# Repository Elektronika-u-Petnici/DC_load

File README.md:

# DC load

Petničko linearno opterećenje

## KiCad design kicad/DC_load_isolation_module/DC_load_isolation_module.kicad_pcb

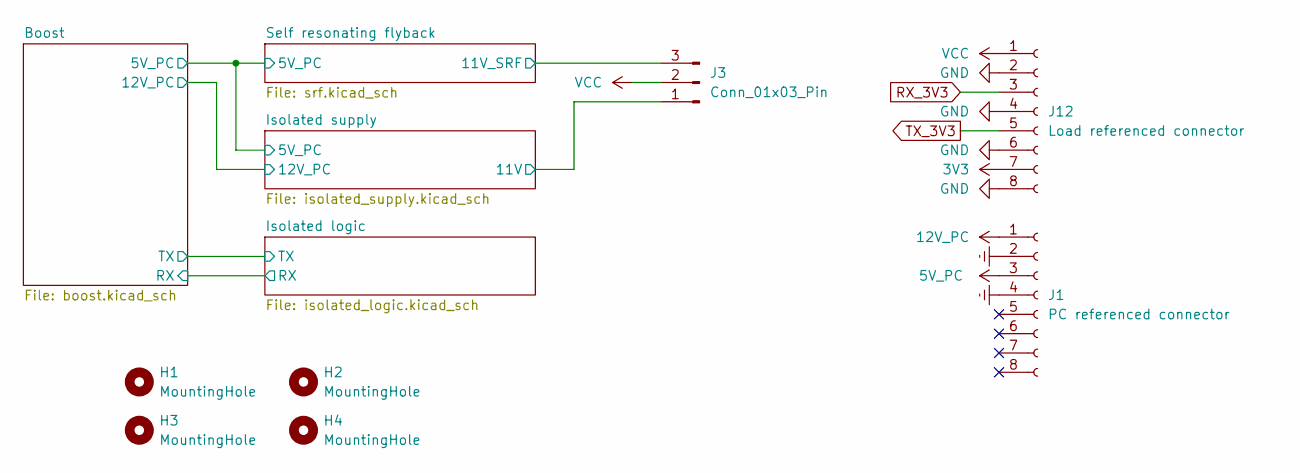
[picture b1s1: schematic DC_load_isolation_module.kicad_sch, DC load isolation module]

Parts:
H1, H2, H3, H4: MountingHole; M3_hole_with_spacer
J1: PC referenced connector; PinSocket_1x08_P2.54mm_Vertical
J3: Conn_01x03_Pin; PinHeader_1x03_P2.54mm_Vertical
J12: Load referenced connector; PinSocket_1x08_P2.54mm_Vertical

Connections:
3V3: J12.7; also elsewhere on the board
5V_PC: J1.3; also elsewhere on the board
12V_PC: J1.1; also elsewhere on the board
/Isolated supply/11V: J3.1; also elsewhere on the board
/Self resonating flyback/11V_SRF: J3.3; also elsewhere on the board
Earth: J1.2, J1.4; also elsewhere on the board
GND: J12.2, J12.4, J12.6, J12.8; also elsewhere on the board
RX_3V3: J12.3; also elsewhere on the board
TX_3V3: J12.5; also elsewhere on the board
VCC: J3.2, J12.1

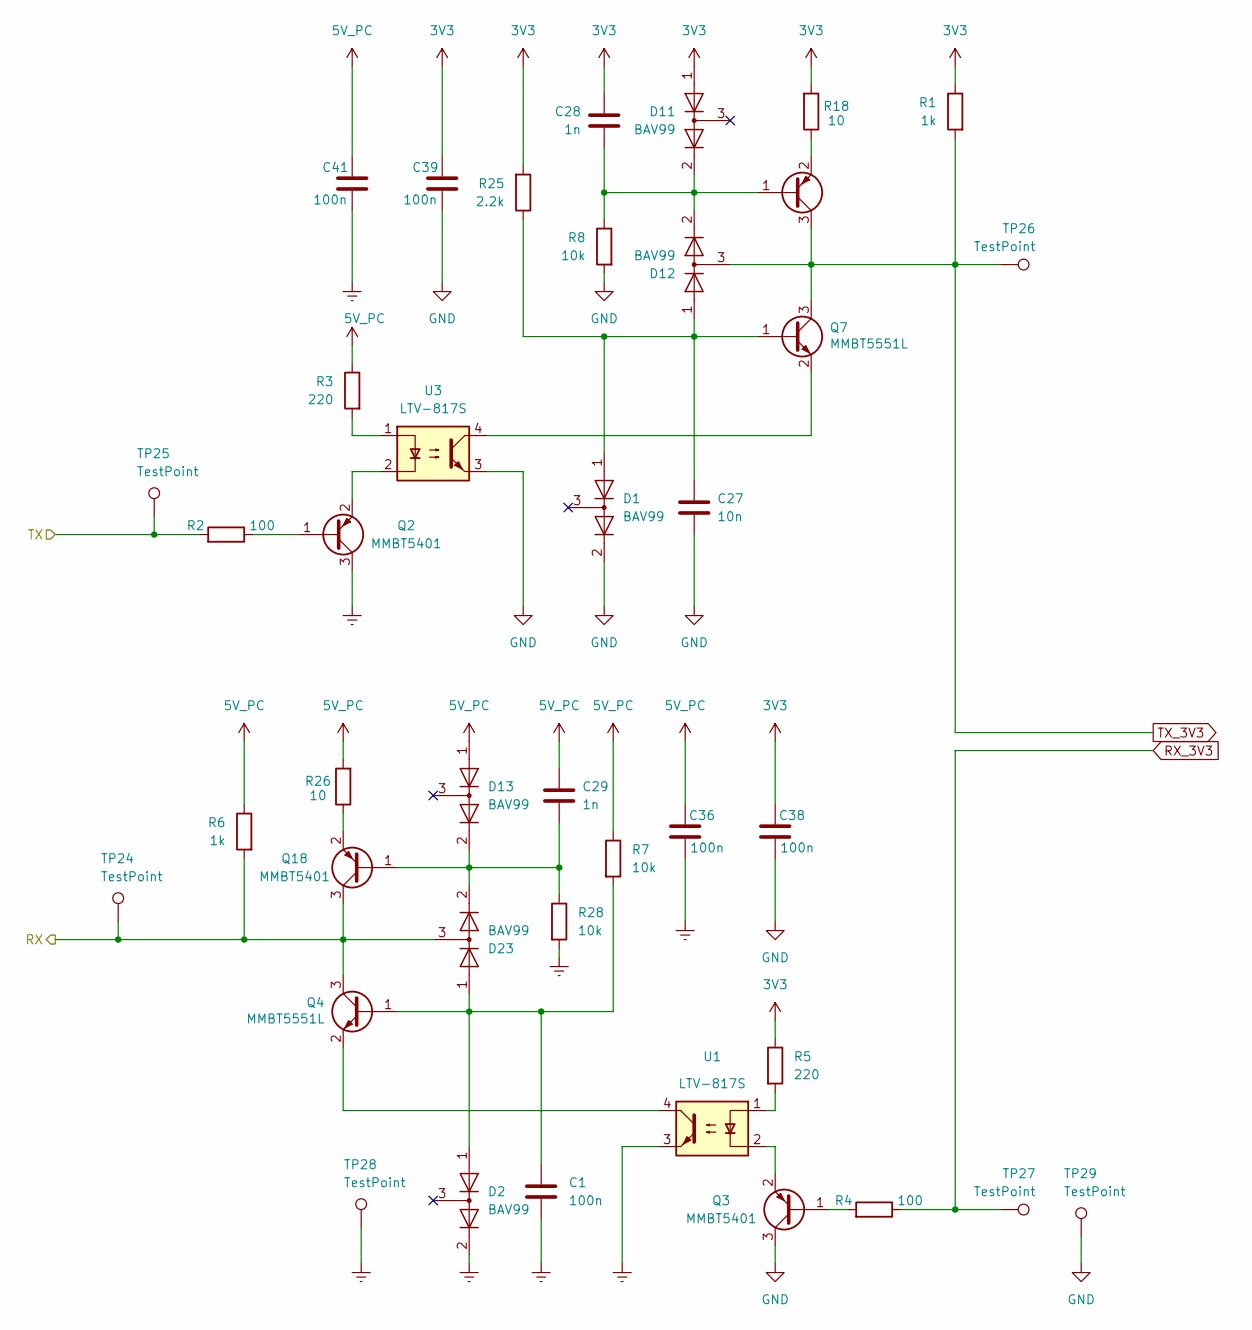
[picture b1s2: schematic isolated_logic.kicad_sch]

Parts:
C1, C36, C38, C39, C41: 100n; C_0603_1608Metric_Pad1.08x0.95mm_HandSolder; LCSC C14663
C27: 10n; C_0603_1608Metric_Pad1.08x0.95mm_HandSolder; LCSC C57112
C28, C29: 1n; C_0603_1608Metric_Pad1.08x0.95mm_HandSolder; LCSC C1588
D1, D2, D11, D12, D13, D23: BAV99; SOT-23; LCSC C2500
Q2, Q3, Q17, Q18: MMBT5401; SOT-23; LCSC C8326
Q4, Q7: MMBT5551L; SOT-23; LCSC C2145
R1, R6: 1k; R_0603_1608Metric_Pad0.98x0.95mm_HandSolder; LCSC C22962
R2, R4: 100; R_0603_1608Metric_Pad0.98x0.95mm_HandSolder; LCSC C22775
R3, R5: 220; R_0603_1608Metric_Pad0.98x0.95mm_HandSolder; LCSC C22962
R7, R8, R28: 10k; R_0603_1608Metric_Pad0.98x0.95mm_HandSolder; LCSC C25804
R18, R26: 10; R_0603_1608Metric_Pad0.98x0.95mm_HandSolder; LCSC C22859
R25: 2.2k; R_0603_1608Metric_Pad0.98x0.95mm_HandSolder; LCSC C4190
TP24, TP25, TP26, TP27, TP28, TP29: TestPoint; TestPoint_Pad_D2.0mm
U1, U3: LTV-817S; SMDIP-4_W9.53mm

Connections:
3V3: C28.2, C38.1, C39.1, D11.1 (K), R1.1, R5.1, R18.2, R25.2; also elsewhere on the board
5V_PC: C29.2, C36.1, C41.1, D13.1 (K), R3.1, R6.1, R7.1, R26.2; also elsewhere on the board
/Boost/RX: D23.3 (K), Q4.3 (C), Q18.3 (C), R6.2, TP24.1; also elsewhere on the board
/Boost/TX: R2.2, TP25.1; also elsewhere on the board
Earth: C1.1, C36.2, C41.2, D2.2 (A), Q2.3 (C), R28.2, TP28.1, U1.3; also elsewhere on the board
GND: C27.1, C38.2, C39.2, D1.2 (A), Q3.3 (C), R8.2, TP29.1, U3.3; also elsewhere on the board
unnamed: C28.1, D11.2 (A), D12.2 (A), Q17.1 (B), R8.1
unnamed: C29.1, D13.2 (A), D23.2 (A), Q18.1 (B), R28.1
unnamed: Q2.1 (B), R2.1
unnamed: Q2.2 (E), U3.2
unnamed: Q3.1 (B), R4.2
unnamed: Q3.2 (E), U1.2
unnamed: C1.2, D2.1 (K), D23.1 (K), Q4.1 (B), R7.2
unnamed: Q4.2 (E), U1.4
unnamed: C27.2, D1.1 (K), D12.1 (K), Q7.1 (B), R25.1
unnamed: Q7.2 (E), U3.4
unnamed: Q17.2 (E), R18.1
unnamed: Q18.2 (E), R26.1
unnamed: R3.2, U3.1
unnamed: R5.2, U1.1
RX_3V3: R4.1, TP27.1; also elsewhere on the board
TX_3V3: D12.3 (K), Q7.3 (C), Q17.3 (C), R1.2, TP26.1; also elsewhere on the board

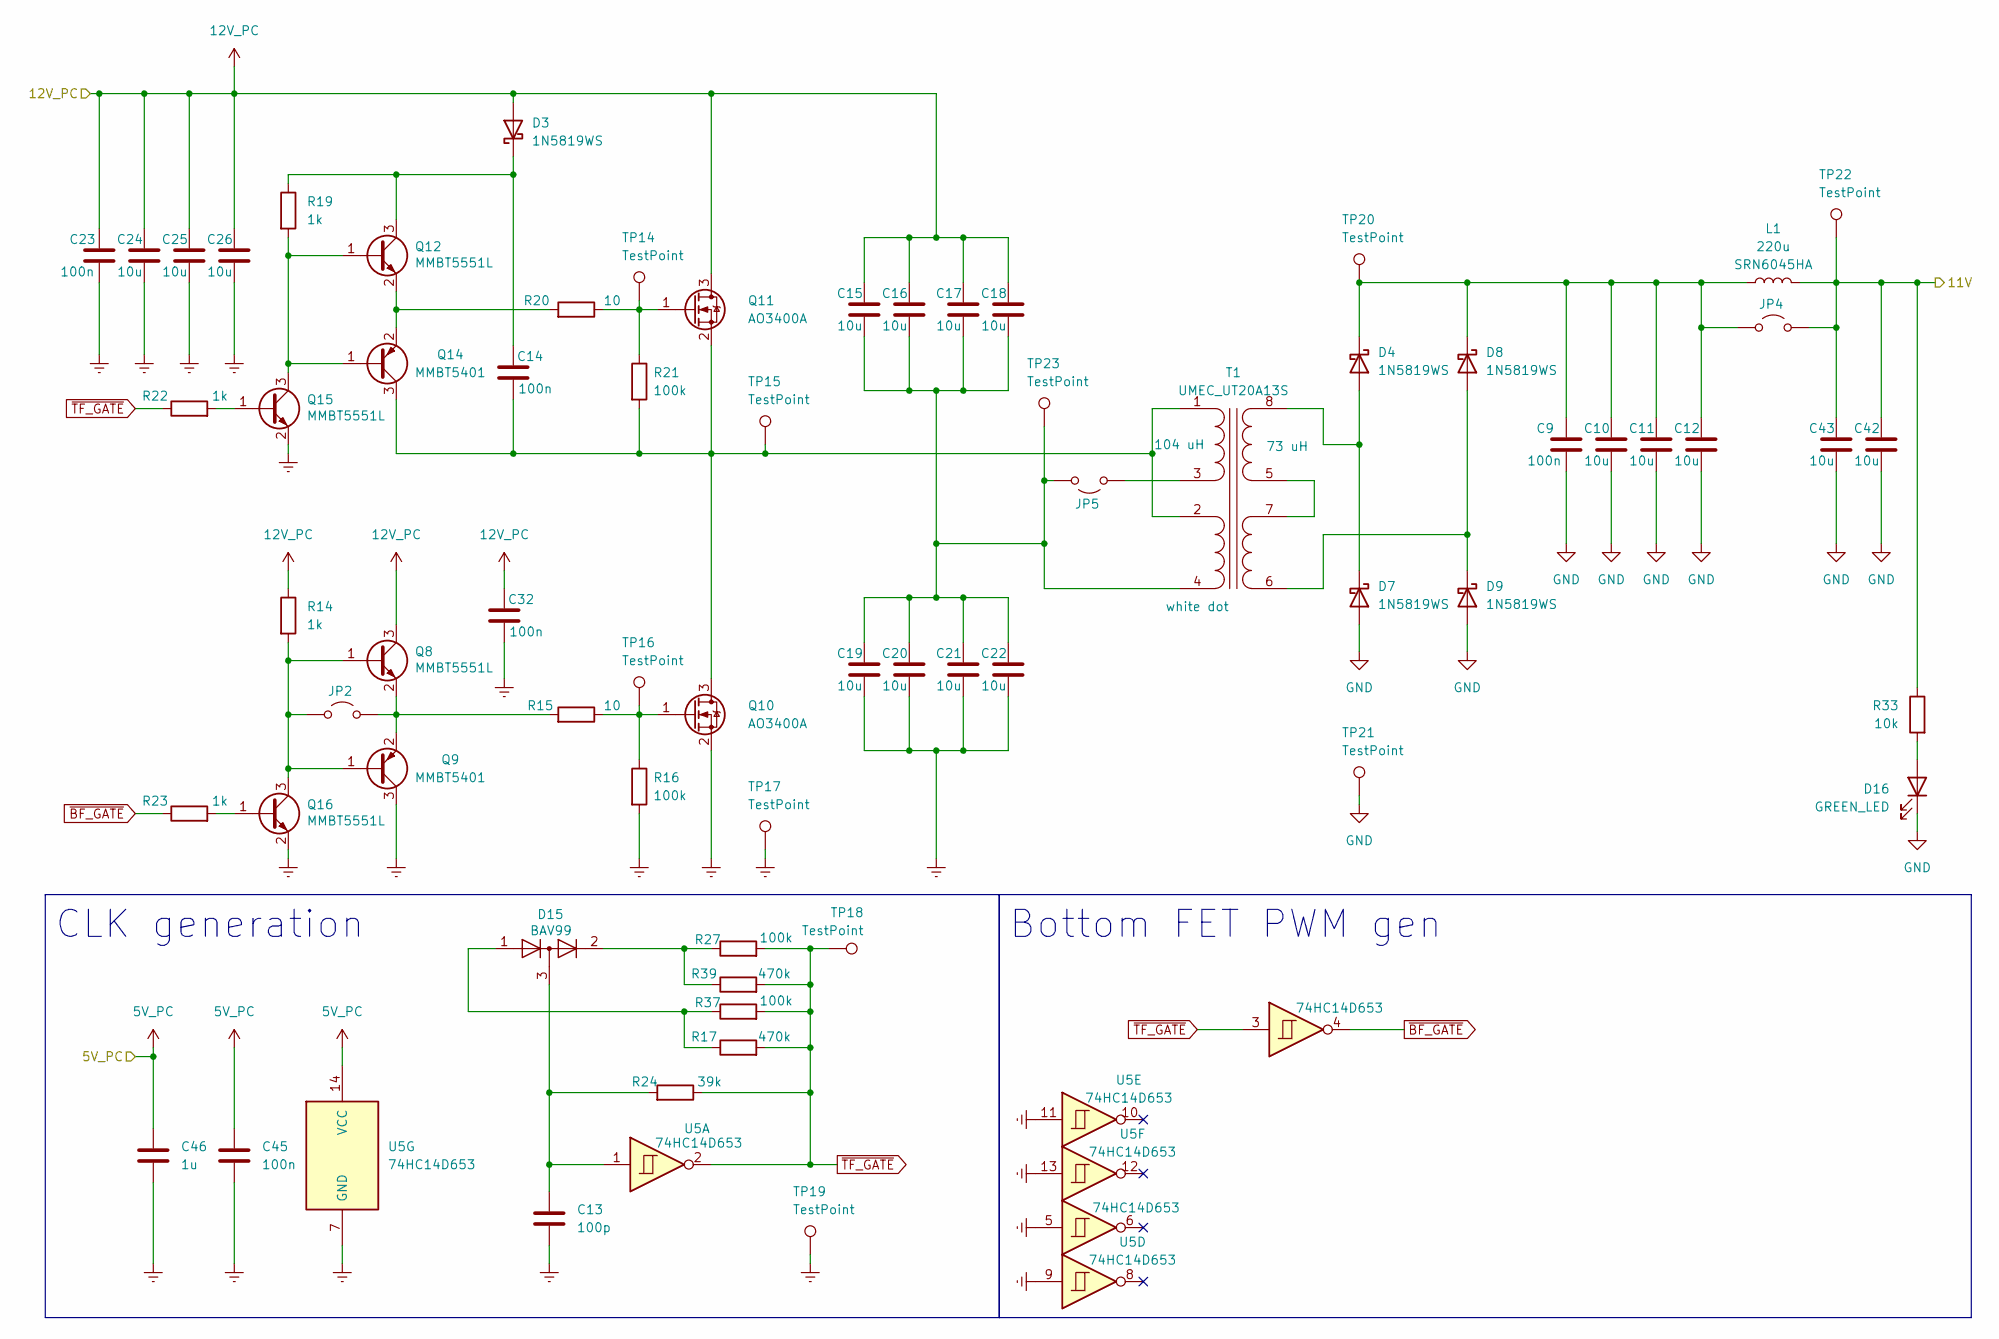
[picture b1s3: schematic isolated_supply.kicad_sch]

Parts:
C9, C14, C23, C32, C45: 100n; C_0603_1608Metric_Pad1.08x0.95mm_HandSolder; LCSC C14663
C10, C11, C12, C15, C16, C17, C18, C19, C20, C21, C22, C24, C25, C26, C42, C43: 10u; C_0603_1608Metric_Pad1.08x0.95mm_HandSolder; LCSC C96446
C13: 100p; C_0603_1608Metric_Pad1.08x0.95mm_HandSolder; LCSC C14858
C46: 1u; C_0603_1608Metric_Pad1.08x0.95mm_HandSolder; LCSC C15849
D3, D4, D7, D8, D9: 1N5819WS; D_SOD-323; LCSC C191023
D15: BAV99; SOT-23; LCSC C2500
D16: GREEN_LED; LED_0805_2012Metric_Pad1.15x1.40mm_HandSolder; LCSC C2297
JP2, JP4, JP5: Jumper_2_Open; SolderJumper-2_P1.3mm_Open_RoundedPad1.0x1.5mm
L1: 220u; L_Bourns_SRN6045TA; Partname SRN6045HA
Q8, Q12, Q15, Q16: MMBT5551L; SOT-23; LCSC C2145
Q9, Q14: MMBT5401; SOT-23; LCSC C8326
Q10, Q11: AO3400A; SOT-23; LCSC C20917
R14, R19, R22, R23: 1k; R_0603_1608Metric_Pad0.98x0.95mm_HandSolder; LCSC C22962
R15, R20: 10; R_0603_1608Metric_Pad0.98x0.95mm_HandSolder; LCSC C22859
R16, R21, R27, R37: 100k; R_0603_1608Metric_Pad0.98x0.95mm_HandSolder; LCSC C25803
R17, R39: 470k; R_0603_1608Metric_Pad0.98x0.95mm_HandSolder; LCSC C23178
R24: 39k; R_0603_1608Metric_Pad0.98x0.95mm_HandSolder; LCSC C23153
R33: 10k; R_0603_1608Metric_Pad0.98x0.95mm_HandSolder; LCSC C25804
T1: UMEC_UT20A13S
TP14, TP15, TP16, TP17, TP18, TP19, TP20, TP21, TP22, TP23: TestPoint; TestPoint_Pad_D2.0mm
U5: 74HC14D653; SOIC-14_3.9x8.7mm_P1.27mm; LCSC C5605

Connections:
5V_PC: C45.2, C46.2, U5.14 (VCC); also elsewhere on the board
12V_PC: C15.1, C16.1, C17.1, C18.1, C23.1, C24.1, C25.1, C26.1, C32.1, D3.2 (A), Q8.3 (C), Q11.3 (D), R14.1; also elsewhere on the board
/Isolated supply/11V: C42.1, C43.1, JP4.2 (B), L1.2, R33.1, TP22.1; also elsewhere on the board
Earth: C13.1, C19.2, C20.2, C21.2, C22.2, C23.2, C24.2, C25.2, C26.2, C32.2, C45.1, C46.1, Q9.3 (C), Q10.2 (S), Q15.2 (E), Q16.2 (E), R16.2, TP17.1, TP19.1, U5.5, U5.7 (GND), U5.9, U5.11, U5.13; also elsewhere on the board
GND: C9.2, C10.2, C11.2, C12.2, C42.2, C43.2, D7.2 (A), D9.2 (A), D16.1 (K), TP21.1; also elsewhere on the board
unnamed: C13.2, D15.3 (K), R24.2, U5.1
unnamed: C14.1, D3.1 (K), Q12.3 (C), R19.1
unnamed: D4.2 (A), D7.1 (K), T1.8 (SB)
unnamed: C9.1, C10.1, C11.1, C12.1, D4.1 (K), D8.1 (K), JP4.1 (A), L1.1, TP20.1
unnamed: D8.2 (A), D9.1 (K), T1.6 (SA)
unnamed: D15.2 (A), R27.1, R39.1
unnamed: D15.1 (K), R17.1, R37.1
unnamed: D16.2 (A), R33.2
unnamed: JP2.1 (A), Q8.1 (B), Q9.1 (B), Q16.3 (C), R14.2
unnamed: JP2.2 (B), Q8.2 (E), Q9.2 (E), R15.2
unnamed: C15.2, C16.2, C17.2, C18.2, C19.1, C20.1, C21.1, C22.1, JP5.1 (A), T1.4 (AB), TP23.1
unnamed: JP5.2 (B), T1.3 (AB)
unnamed: C14.2, Q10.3 (D), Q11.2 (S), Q14.3 (C), R21.2, T1.1 (AA), T1.2 (AA), TP15.1
unnamed: Q10.1 (G), R15.1, R16.1, TP16.1
unnamed: Q11.1 (G), R20.1, R21.1, TP14.1
unnamed: Q12.1 (B), Q14.1 (B), Q15.3 (C), R19.2
unnamed: Q12.2 (E), Q14.2 (E), R20.2
unnamed: Q15.1 (B), R22.2
unnamed: Q16.1 (B), R23.2
unnamed: T1.5 (SA), T1.7 (SB)
~BF_GATE: R23.1, U5.4
~TF_GATE: R17.2, R22.1, R24.1, R27.2, R37.2, R39.2, TP18.1, U5.2, U5.3

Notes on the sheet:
Bottom FET PWM gen
CLK generation

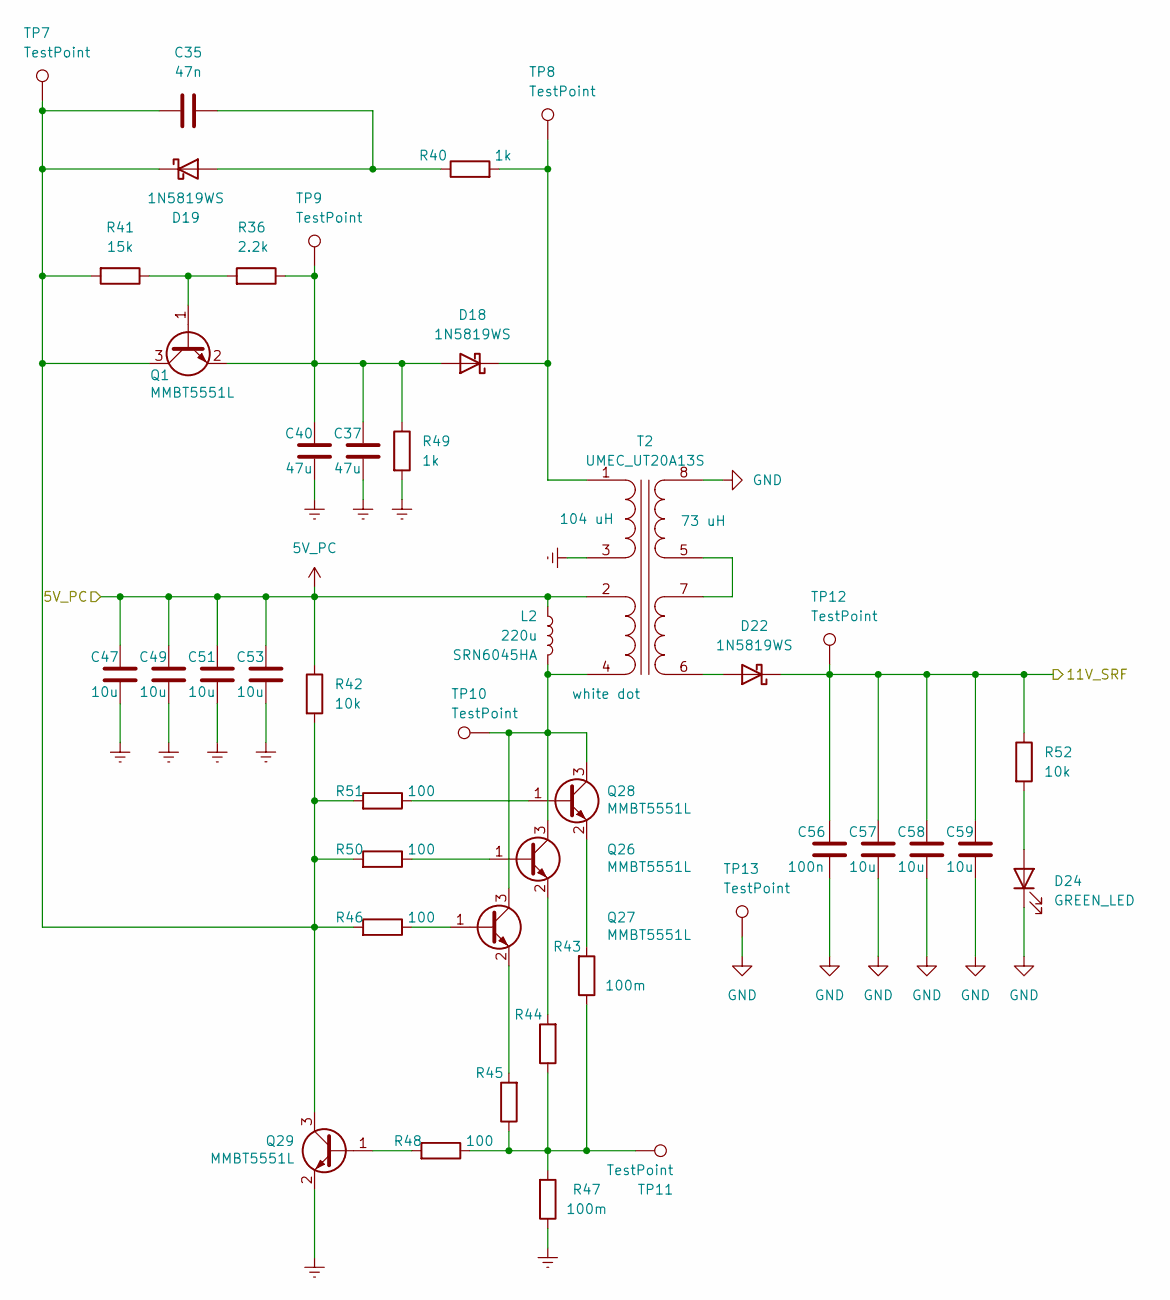
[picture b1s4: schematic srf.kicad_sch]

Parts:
C35: 47n; C_0603_1608Metric_Pad1.08x0.95mm_HandSolder; LCSC C1622
C37, C40: 47u; C_1206_3216Metric_Pad1.33x1.80mm_HandSolder; LCSC C96123
C47, C49, C51, C53, C57, C58, C59: 10u; C_0603_1608Metric_Pad1.08x0.95mm_HandSolder; LCSC C96446
C56: 100n; C_0603_1608Metric_Pad1.08x0.95mm_HandSolder; LCSC C14663
D18, D19, D22: 1N5819WS; D_SOD-323; LCSC C191023
D24: GREEN_LED; LED_0805_2012Metric_Pad1.15x1.40mm_HandSolder; LCSC C2297
L2: 220u; L_Bourns_SRN6045TA; Partname SRN6045HA
Q1, Q26, Q27, Q28, Q29: MMBT5551L; SOT-23; LCSC C2145
R36: 2.2k; R_0603_1608Metric_Pad0.98x0.95mm_HandSolder; LCSC C4190
R40, R49: 1k; R_0603_1608Metric_Pad0.98x0.95mm_HandSolder; LCSC C22962
R41: 15k; R_0603_1608Metric_Pad0.98x0.95mm_HandSolder; LCSC C22809
R42, R52: 10k; R_0603_1608Metric_Pad0.98x0.95mm_HandSolder; LCSC C25804
R43, R44, R45, R47: 100m; R_1206_3216Metric_Pad1.30x1.75mm_HandSolder; LCSC C25334
R46, R48, R50, R51: 100; R_0603_1608Metric_Pad0.98x0.95mm_HandSolder; LCSC C22775
T2: UMEC_UT20A13S
TP7, TP8, TP9, TP10, TP11, TP12, TP13: TestPoint; TestPoint_Pad_D2.0mm

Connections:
5V_PC: C47.1, C49.1, C51.1, C53.1, L2.2, R42.1, T2.2 (AA); also elsewhere on the board
/Self resonating flyback/11V_SRF: C56.1, C57.1, C58.1, C59.1, D22.1 (K), R52.1, TP12.1; also elsewhere on the board
Earth: C37.2, C40.2, C47.2, C49.2, C51.2, C53.2, Q29.2 (E), R47.1, R49.2, T2.3 (AB); also elsewhere on the board
GND: C56.2, C57.2, C58.2, C59.2, D24.1 (K), T2.8 (SB), TP13.1; also elsewhere on the board
unnamed: C37.1, C40.1, D18.2 (A), Q1.2 (E), R36.1, R49.1, TP9.1
unnamed: D18.1 (K), R40.2, T2.1 (AA), TP8.1
unnamed: C35.2, D19.2 (A), R40.1
unnamed: C35.1, D19.1 (K), Q1.3 (C), Q29.3 (C), R41.2, R42.2, R46.2, R50.2, R51.2, TP7.1
unnamed: D22.2 (A), T2.6 (SA)
unnamed: D24.2 (A), R52.2
unnamed: Q1.1 (B), R36.2, R41.1
unnamed: Q26.1 (B), R50.1
unnamed: L2.1, Q26.3 (C), Q27.3 (C), Q28.3 (C), T2.4 (AB), TP10.1
unnamed: Q26.2 (E), R44.2
unnamed: Q27.1 (B), R46.1
unnamed: Q27.2 (E), R45.2
unnamed: Q28.1 (B), R51.1
unnamed: Q28.2 (E), R43.2
unnamed: Q29.1 (B), R48.2
unnamed: R43.1, R44.1, R45.1, R47.2, R48.1, TP11.1
unnamed: T2.5 (SA), T2.7 (SB)

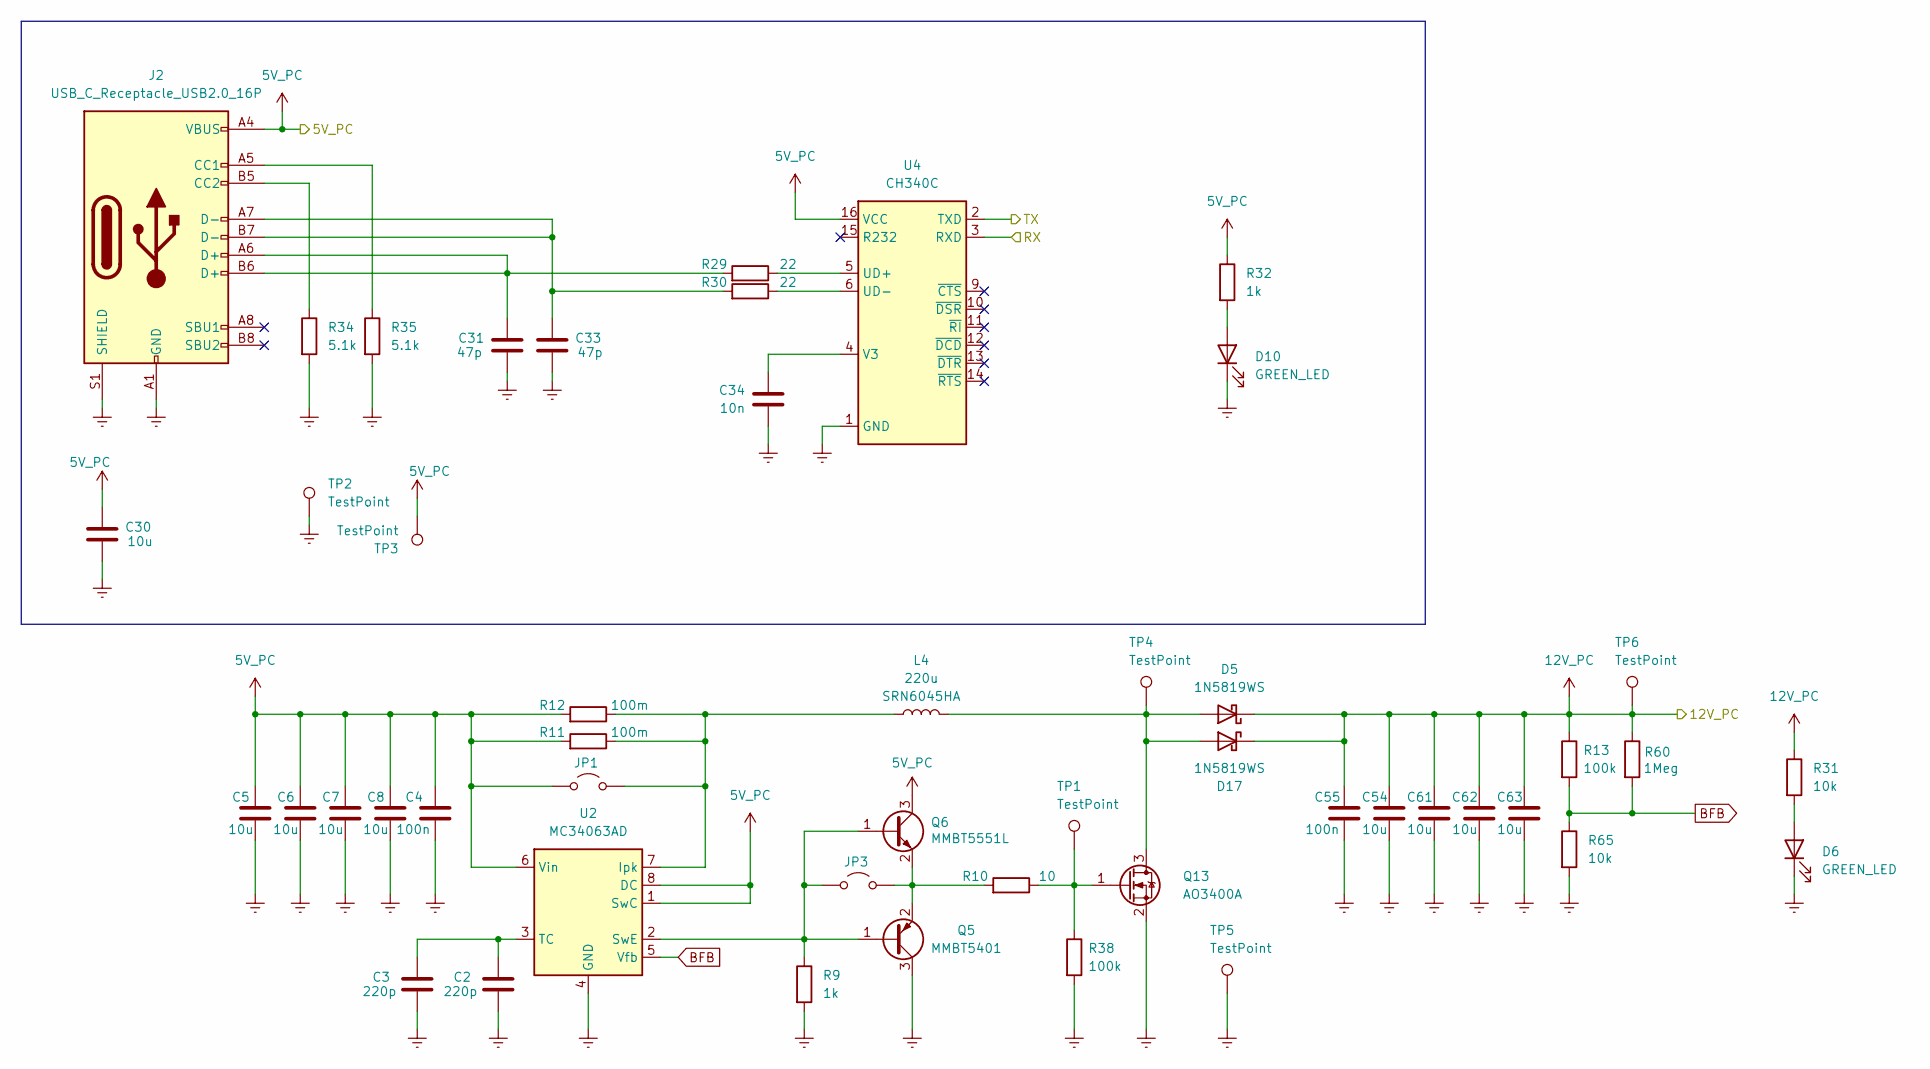
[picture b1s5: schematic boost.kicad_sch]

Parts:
C2, C3: 220p; C_0603_1608Metric_Pad1.08x0.95mm_HandSolder; LCSC C1603
C4, C55: 100n; C_0603_1608Metric_Pad1.08x0.95mm_HandSolder; LCSC C14663
C5, C6, C7, C8, C30, C54, C61, C62, C63: 10u; C_0603_1608Metric_Pad1.08x0.95mm_HandSolder; LCSC C96446
C31, C33: 47p; C_0603_1608Metric_Pad1.08x0.95mm_HandSolder; LCSC C1671
C34: 10n; C_0603_1608Metric_Pad1.08x0.95mm_HandSolder; LCSC C57112
D5, D17: 1N5819WS; D_SOD-323; LCSC C191023
D6, D10: GREEN_LED; LED_0805_2012Metric_Pad1.15x1.40mm_HandSolder; LCSC C2297
J2: USB_C_Receptacle_USB2.0_16P; USB_C_Receptacle_G-Switch_GT-USB-7010ASV
JP1, JP3: Jumper_2_Open; SolderJumper-2_P1.3mm_Open_RoundedPad1.0x1.5mm
L4: 220u; L_Bourns_SRN6045TA; Partname SRN6045HA
Q5: MMBT5401; SOT-23; LCSC C8326
Q6: MMBT5551L; SOT-23; LCSC C2145
Q13: AO3400A; SOT-23; LCSC C20917
R9, R32: 1k; R_0603_1608Metric_Pad0.98x0.95mm_HandSolder; LCSC C22962
R10: 10; R_0603_1608Metric_Pad0.98x0.95mm_HandSolder; LCSC C22859
R11, R12: 100m; R_1206_3216Metric_Pad1.30x1.75mm_HandSolder; LCSC C25334
R13, R38: 100k; R_0603_1608Metric_Pad0.98x0.95mm_HandSolder; LCSC C25803
R29, R30: 22; R_0603_1608Metric_Pad0.98x0.95mm_HandSolder; LCSC C23345
R31, R65: 10k; R_0603_1608Metric_Pad0.98x0.95mm_HandSolder; LCSC C25804
R34, R35: 5.1k; R_0603_1608Metric_Pad0.98x0.95mm_HandSolder; LCSC C23186
R60: 1Meg; R_0603_1608Metric_Pad0.98x0.95mm_HandSolder; LCSC C22935
TP1, TP2, TP3, TP4, TP5, TP6: TestPoint; TestPoint_Pad_D2.0mm
U2: MC34063AD; SOIC-8_3.9x4.9mm_P1.27mm
U4: CH340C; SOIC-16_3.9x9.9mm_P1.27mm

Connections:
5V_PC: C4.1, C5.1, C6.1, C7.1, C8.1, C30.1, J2.A4 (VBUS), J2.A9 (VBUS), J2.B4 (VBUS), J2.B9 (VBUS), JP1.1 (A), Q6.3 (C), R11.2, R12.2, R32.1, TP3.1, U2.1 (SwC), U2.6 (Vin), U2.8 (DC), U4.16 (VCC); also elsewhere on the board
12V_PC: C54.1, C55.1, C61.1, C62.1, C63.1, D5.1 (K), D17.1 (K), R13.1, R31.1, R60.1, TP6.1; also elsewhere on the board
/Boost/RX: U4.3 (RXD); also elsewhere on the board
/Boost/TX: U4.2 (TXD); also elsewhere on the board
BFB: R13.2, R60.2, R65.1, U2.5 (Vfb)
Earth: C2.2, C3.2, C4.2, C5.2, C6.2, C7.2, C8.2, C30.2, C31.2, C33.2, C34.1, C54.2, C55.2, C61.2, C62.2, C63.2, D6.1 (K), D10.1 (K), J2.A1 (GND), J2.A12 (GND), J2.B1 (GND), J2.B12 (GND), J2.S1 (SHIELD), Q5.3 (C), Q13.2 (S), R9.2, R34.2, R35.2, R38.2, R65.2, TP2.1, TP5.1, U2.4 (GND), U4.1 (GND); also elsewhere on the board
unnamed: C31.1, J2.A6 (D+), J2.B6 (D+), R29.2
unnamed: C33.1, J2.A7 (D-), J2.B7 (D-), R30.2
unnamed: D6.2 (A), R31.2
unnamed: D10.2 (A), R32.2
unnamed: D5.2 (A), D17.2 (A), L4.2, Q13.3 (D), TP4.1
unnamed: J2.A5 (CC1), R35.1
unnamed: J2.B5 (CC2), R34.1
unnamed: JP1.2 (B), L4.1, R11.1, R12.1, U2.7 (Ipk)
unnamed: JP3.1 (A), Q5.1 (B), Q6.1 (B), R9.1, U2.2 (SwE)
unnamed: JP3.2 (B), Q5.2 (E), Q6.2 (E), R10.2
unnamed: Q13.1 (G), R10.1, R38.1, TP1.1
unnamed: C2.1, C3.1, U2.3 (TC)
unnamed: R29.1, U4.5 (UD+)
unnamed: R30.1, U4.6 (UD-)
unnamed: C34.2, U4.4 (V3)

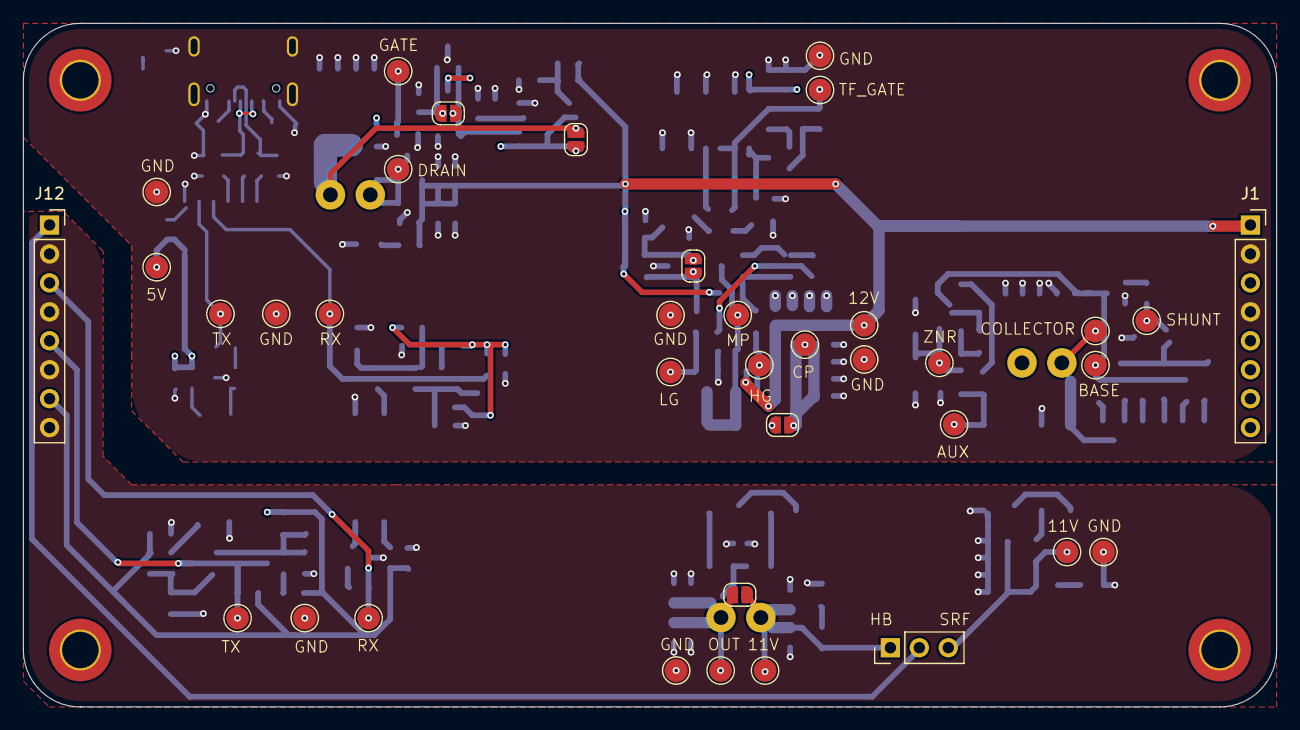
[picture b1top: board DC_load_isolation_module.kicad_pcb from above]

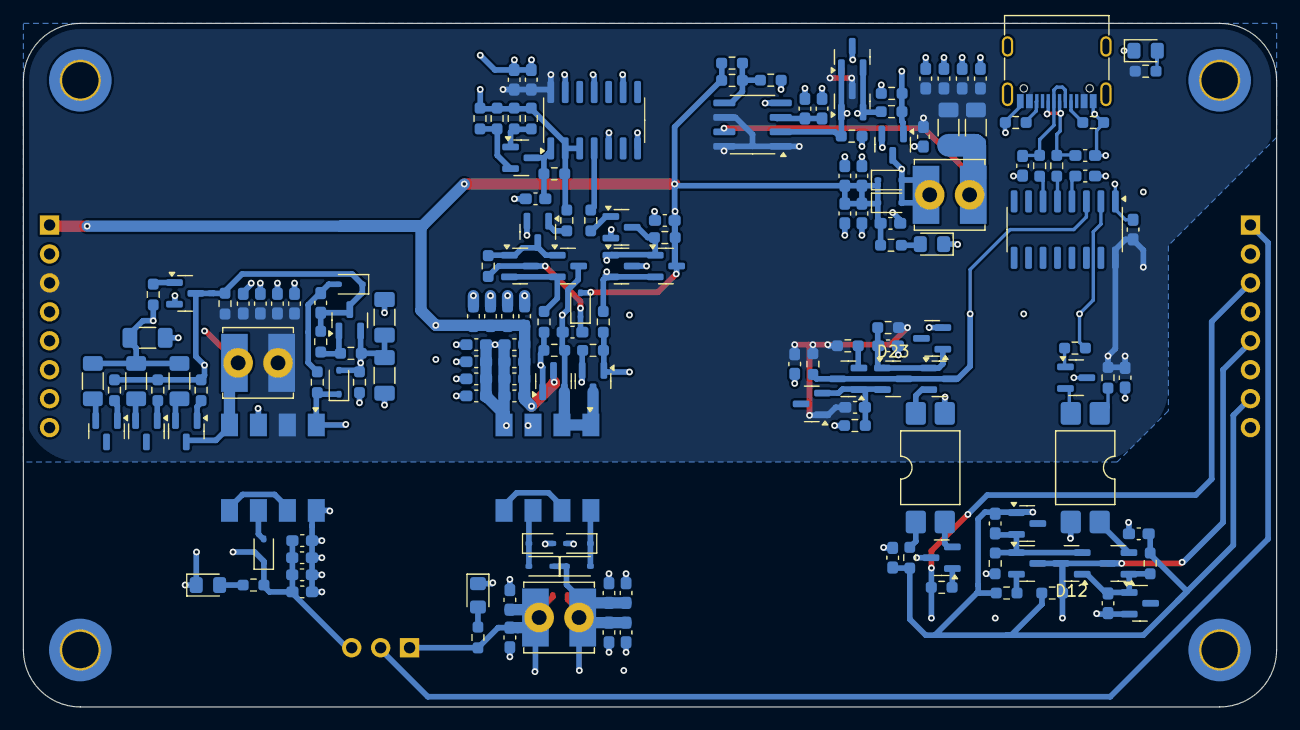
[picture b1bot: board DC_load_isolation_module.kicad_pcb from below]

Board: 2 copper layers, 110.0 x 60.0 mm, 207 parts (166 on the bottom side), 81 nets.

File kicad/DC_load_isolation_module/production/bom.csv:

Designator,Footprint,Quantity,Value,LCSC Part #
"C1, C14, C23, C32, C36, C38, C39, C4, C41, C45, C55, C56, C9",0603,13,100n,C14663
"C10, C11, C12, C15, C16, C17, C18, C19, C20, C21, C22, C24, C25, C26, C30, C42, C43, C47, C49, C5, C51, C53, C54, C57, C58, C59, C6, C61, C62, C63, C7, C8",0603,32,10u,C96446
C13,0603,1,100p,C14858
"C2, C3",0603,2,220p,C1603
"C27, C34",0603,2,10n,C57112
"C28, C29",0603,2,1n,C1588
"C31, C33",0603,2,47p,C1671
C35,0603,1,47n,C1622
"C37, C40",1206,2,47u,C96123
C46,0603,1,1u,C15849
"D1, D11, D12, D13, D15, D2, D23",SOT-23,7,BAV99,C2500
"D10, D16, D24, D6",0805,4,GREEN_LED,C2297
"D17, D18, D19, D22, D3, D4, D5, D7, D8, D9",D_SOD-323,10,1N5819WS,C191023
J1,PinSocket_1x08_P2.54mm_Vertical,1,PC referenced connector,
J12,PinSocket_1x08_P2.54mm_Vertical,1,Load referenced connector,
J2,USB_C_Receptacle_G-Switch_GT-USB-7010ASV,1,USB_C_Receptacle_USB2.0_16P,
J3,PinHeader_1x03_P2.54mm_Vertical,1,Conn_01x03_Pin,
"JP1, JP2, JP3, JP4, JP5",SolderJumper-2_P1.3mm_Open_RoundedPad1.0x1.5mm,5,Jumper_2_Open,
"L1, L2, L4",L_Bourns_SRN6045TA,3,220u,
"Q1, Q12, Q15, Q16, Q26, Q27, Q28, Q29, Q4, Q6, Q7, Q8",SOT-23,12,MMBT5551L,C2145
"Q10, Q11, Q13",SOT-23,3,AO3400A,C20917
"Q14, Q17, Q18, Q2, Q3, Q5, Q9",SOT-23,7,MMBT5401,C8326
"R1, R14, R19, R22, R23, R32, R40, R49, R6, R9",0603,10,1k,C22962
"R10, R15, R18, R20, R26",0603,5,10,C22859
"R11, R12, R43, R44, R45, R47",1206,6,100m,C25334
"R13, R16, R21, R27, R37, R38",0603,6,100k,C25803
"R17, R39",0603,2,470k,C23178
"R2, R4, R46, R48, R50, R51",0603,6,100,C22775
R24,0603,1,39k,C23153
"R25, R36",0603,2,2.2k,C4190
"R28, R31, R33, R42, R52, R65, R7, R8",0603,8,10k,C25804
"R29, R30",0603,2,22,C23345
"R3, R5",0603,2,220,C22962
"R34, R35",0603,2,5.1k,C23186
R41,0603,1,15k,C22809
R60,0603,1,1Meg,C22935
"T1, T2",UMEC_UT20A13S,2,UMEC_UT20A13S,
"TP1, TP10, TP11, TP12, TP13, TP14, TP15, TP16, TP17, TP18, TP19, TP2, TP20, TP21, TP22, TP23, TP24, TP25, TP26, TP27, TP28, TP29, TP3, TP4, TP5, TP6, TP7, TP8, TP9",TestPoint_Pad_D2.0mm,29,TestPoint,
"U1, U3",SMDIP-4_W9.53mm,2,LTV-817S,
U2,SOIC-8_3.9x4.9mm_P1.27mm,1,MC34063AD,
U4,SOIC-16_3.9x9.9mm_P1.27mm,1,CH340C,
U5,SOIC-14_3.9x8.7mm_P1.27mm,1,74HC14D653,C5605

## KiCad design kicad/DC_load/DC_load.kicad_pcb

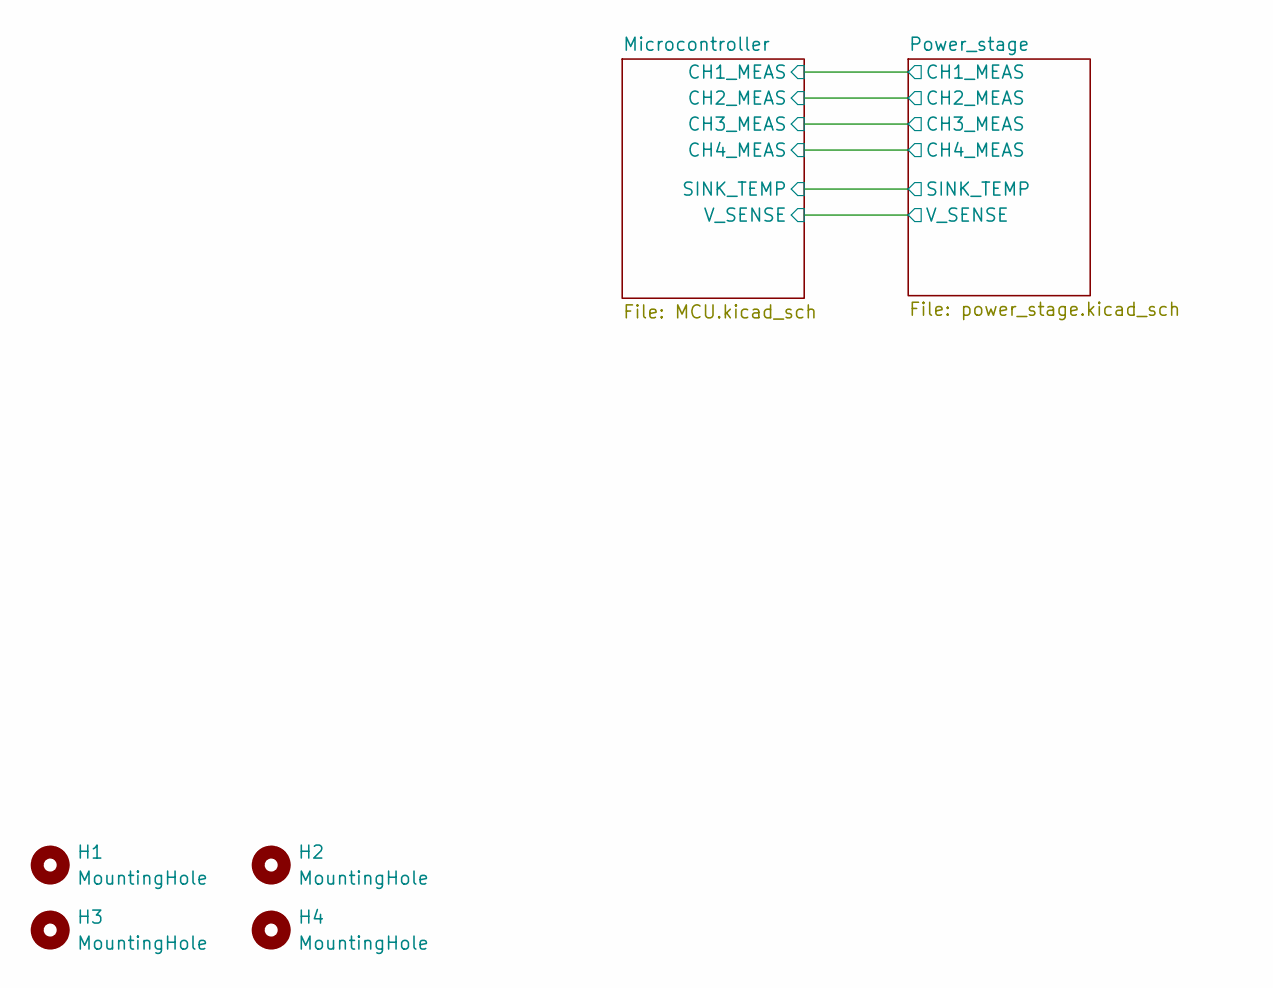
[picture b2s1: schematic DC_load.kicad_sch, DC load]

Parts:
H1, H2, H3, H4: MountingHole; M3_hole_with_spacer
